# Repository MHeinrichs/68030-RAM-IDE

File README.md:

[This project moved to gitlab on the day M$ bought github](https://gitlab.com/MHeinrichs/68030-RAM-IDE)

The new repository is at: https://gitlab.com/MHeinrichs/68030-RAM-IDE

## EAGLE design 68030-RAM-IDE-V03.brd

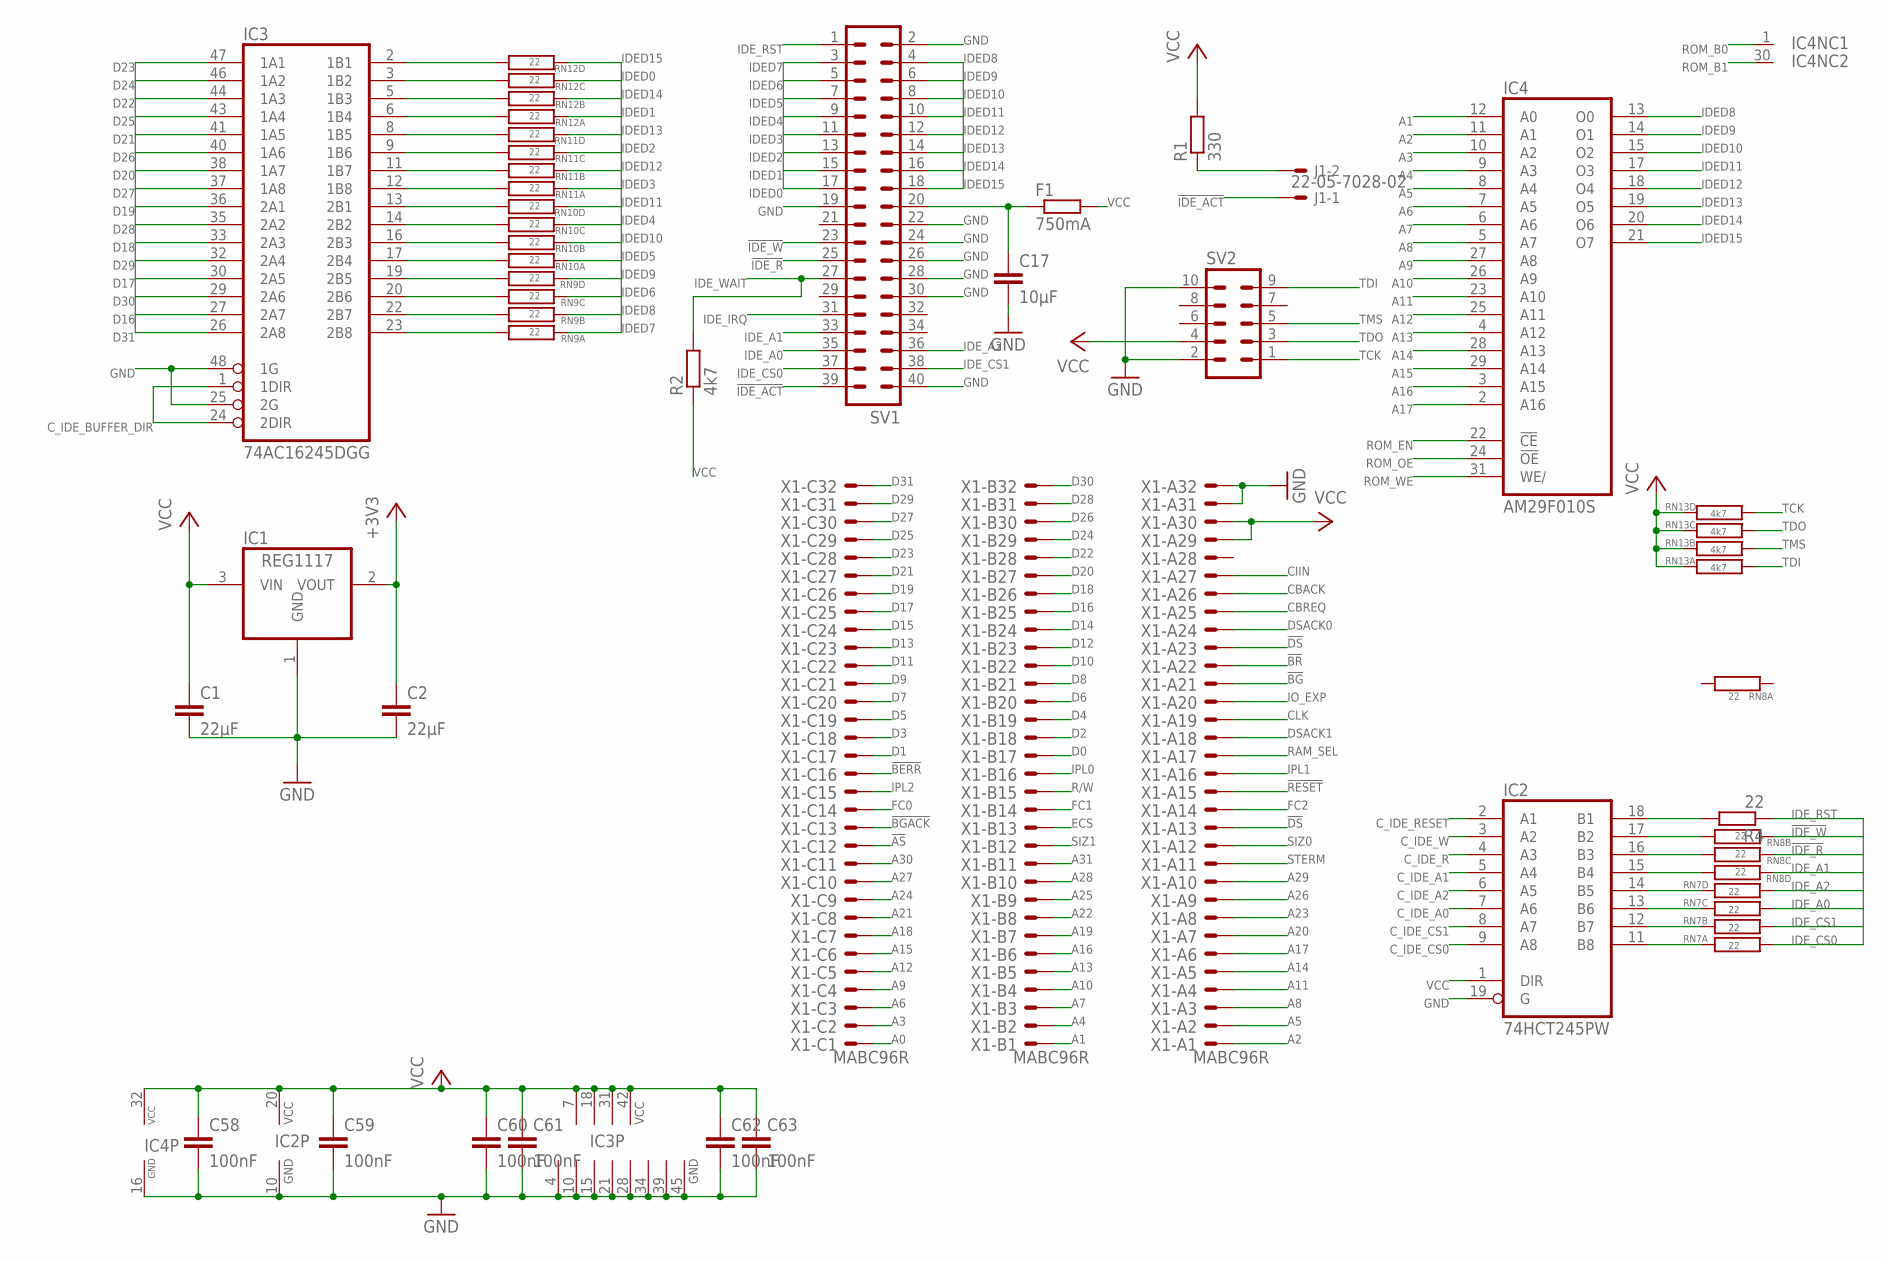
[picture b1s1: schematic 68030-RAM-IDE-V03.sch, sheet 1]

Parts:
C1, C2: 22µF; C1210K
C17: 10µF; C0805K
C58, C59, C60, C61, C62, C63: 100nF; C0805K
F1: 750mA; R2512
IC1: REG1117; SOT223
IC2: 74HCT245PW; TSSOP20
IC3: 74AC16245DGG; TSSOP48
IC4: AM29F010S; PLCC-SR32
J1: 22-05-7028-02; 7395-02
R1: 330; R0805
R2: 4k7; R0805
R4: 22; R0805
RN7, RN8, RN9, RN10, RN11, RN12: 22; R-NETZ@2
RN13: 4k7; R-NETZ@2
SV1: ML40
SV2: ML10
X1: MABC96R

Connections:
!AS: X1.C12; also elsewhere on the board
!BERR: X1.C16
!BG: X1.A21
!BGACK: X1.C13
!BR: X1.A22
!DS: X1.A13, X1.A23; also elsewhere on the board
!IDE_ACT: J1.1, SV1.39
!IDE_R: RN8.P$6, SV1.25
!IDE_W: RN8.P$7, SV1.23
!RESET: X1.A15; also elsewhere on the board
+3V3: C2.1, IC1.2 (VOUT); also elsewhere on the board
A0: X1.C1; also elsewhere on the board
A1: IC4.12 (A0), X1.B1; also elsewhere on the board
A2: IC4.11 (A1), X1.A1; also elsewhere on the board
A3: IC4.10 (A2), X1.C2; also elsewhere on the board
A4: IC4.9 (A3), X1.B2; also elsewhere on the board
A5: IC4.8 (A4), X1.A2; also elsewhere on the board
A6: IC4.7 (A5), X1.C3; also elsewhere on the board
A7: IC4.6 (A6), X1.B3; also elsewhere on the board
A8: IC4.5 (A7), X1.A3; also elsewhere on the board
A9: IC4.27 (A8), X1.C4; also elsewhere on the board
A10: IC4.26 (A9), X1.B4; also elsewhere on the board
A11: IC4.23 (A10), X1.A4; also elsewhere on the board
A12: IC4.25 (A11), X1.C5; also elsewhere on the board
A13: IC4.4 (A12), X1.B5; also elsewhere on the board
A14: IC4.28 (A13), X1.A5; also elsewhere on the board
A15: IC4.29 (A14), X1.C6; also elsewhere on the board
A16: IC4.3 (A15), X1.B6; also elsewhere on the board
A17: IC4.2 (A16), X1.A6; also elsewhere on the board
A18: X1.C7; also elsewhere on the board
A19: X1.B7; also elsewhere on the board
A20: X1.A7; also elsewhere on the board
A21: X1.C8; also elsewhere on the board
A22: X1.B8; also elsewhere on the board
A23: X1.A8; also elsewhere on the board
A24: X1.C9; also elsewhere on the board
A25: X1.B9; also elsewhere on the board
A26: X1.A9; also elsewhere on the board
A27: X1.C10; also elsewhere on the board
A28: X1.B10; also elsewhere on the board
A29: X1.A10; also elsewhere on the board
A30: X1.C11; also elsewhere on the board
A31: X1.B11; also elsewhere on the board
CBACK: X1.A26; also elsewhere on the board
CBREQ: X1.A25; also elsewhere on the board
CIIN: X1.A27; also elsewhere on the board
CLK: X1.A19; also elsewhere on the board
C_IDE_A0: IC2.7 (A6); also elsewhere on the board
C_IDE_A1: IC2.5 (A4); also elsewhere on the board
C_IDE_A2: IC2.6 (A5); also elsewhere on the board
C_IDE_BUFFER_DIR: IC3.1 (1DIR), IC3.24 (2DIR); also elsewhere on the board
C_IDE_CS0: IC2.9 (A8); also elsewhere on the board
C_IDE_CS1: IC2.8 (A7); also elsewhere on the board
C_IDE_R: IC2.4 (A3); also elsewhere on the board
C_IDE_RESET: IC2.2 (A1); also elsewhere on the board
C_IDE_W: IC2.3 (A2); also elsewhere on the board
D0: X1.B17; also elsewhere on the board
D1: X1.C17; also elsewhere on the board
D2: X1.B18; also elsewhere on the board
D3: X1.C18; also elsewhere on the board
D4: X1.B19; also elsewhere on the board
D5: X1.C19; also elsewhere on the board
D6: X1.B20; also elsewhere on the board
D7: X1.C20; also elsewhere on the board
D8: X1.B21; also elsewhere on the board
D9: X1.C21; also elsewhere on the board
D10: X1.B22; also elsewhere on the board
D11: X1.C22; also elsewhere on the board
D12: X1.B23; also elsewhere on the board
D13: X1.C23; also elsewhere on the board
D14: X1.B24; also elsewhere on the board
D15: X1.C24; also elsewhere on the board
D16: IC3.27 (2A7), X1.B25; also elsewhere on the board
D17: IC3.30 (2A5), X1.C25; also elsewhere on the board
D18: IC3.33 (2A3), X1.B26; also elsewhere on the board
D19: IC3.36 (2A1), X1.C26; also elsewhere on the board
D20: IC3.38 (1A7), X1.B27; also elsewhere on the board
D21: IC3.41 (1A5), X1.C27; also elsewhere on the board
D22: IC3.44 (1A3), X1.B28; also elsewhere on the board
D23: IC3.47 (1A1), X1.C28; also elsewhere on the board
D24: IC3.46 (1A2), X1.B29; also elsewhere on the board
D25: IC3.43 (1A4), X1.C29; also elsewhere on the board
D26: IC3.40 (1A6), X1.B30; also elsewhere on the board
D27: IC3.37 (1A8), X1.C30; also elsewhere on the board
D28: IC3.35 (2A2), X1.B31; also elsewhere on the board
D29: IC3.32 (2A4), X1.C31; also elsewhere on the board
D30: IC3.29 (2A6), X1.B32; also elsewhere on the board
D31: IC3.26 (2A8), X1.C32; also elsewhere on the board
DSACK0: X1.A24; also elsewhere on the board
DSACK1: X1.A18; also elsewhere on the board
ECS: X1.B13; also elsewhere on the board
FC0: X1.C14
FC1: X1.B14
FC2: X1.A14
GND: C1.2, C2.2, C17.2, C58.2, C59.2, C60.2, C61.2, C62.2, C63.2, IC1.1 (GND), IC2.10 (GND), IC2.19 (G), IC3.4 (GND), IC3.10 (GND), IC3.15 (GND), IC3.21 (GND), IC3.25 (2G), IC3.28 (GND), IC3.34 (GND), IC3.39 (GND), IC3.45 (GND), IC3.48 (1G), IC4.16 (GND), SV1.2, SV1.19, SV1.22, SV1.24, SV1.26, SV1.28, SV1.30, SV1.40, SV2.2, SV2.10, X1.A31, X1.A32; also elsewhere on the board
IDED0: RN12.P$6, SV1.17
IDED1: RN12.P$8, SV1.15
IDED2: RN11.P$6, SV1.13
IDED3: RN11.P$8, SV1.11
IDED4: RN10.P$6, SV1.9
IDED5: RN10.P$8, SV1.7
IDED6: RN9.P$6, SV1.5
IDED7: RN9.P$8, SV1.3
IDED8: IC4.13 (O0), RN9.P$7, SV1.4
IDED9: IC4.14 (O1), RN9.P$5, SV1.6
IDED10: IC4.15 (O2), RN10.P$7, SV1.8
IDED11: IC4.17 (O3), RN10.P$5, SV1.10
IDED12: IC4.18 (O4), RN11.P$7, SV1.12
IDED13: IC4.19 (O5), RN11.P$5, SV1.14
IDED14: IC4.20 (O6), RN12.P$7, SV1.16
IDED15: IC4.21 (O7), RN12.P$5, SV1.18
IDE_A0: RN7.P$3, SV1.35
IDE_A1: RN8.P$5, SV1.33
IDE_A2: RN7.P$4, SV1.36
IDE_CS0: RN7.P$1, SV1.37
IDE_CS1: RN7.P$2, SV1.38
IDE_IRQ: SV1.31
IDE_RST: R4.1, SV1.1
IDE_WAIT: R2.2, SV1.27; also elsewhere on the board
IO_EXP: X1.A20
IPL0: X1.B16
IPL1: X1.A16
IPL2: X1.C15
KEY_PIN_POWER: C17.1, F1.1, SV1.20
unnamed: IC2.12 (B7), RN7.P$7
unnamed: IC2.11 (B8), RN7.P$8
unnamed: IC2.14 (B5), RN7.P$5
unnamed: IC2.13 (B6), RN7.P$6
unnamed: IC2.16 (B3), RN8.P$3
unnamed: IC2.15 (B4), RN8.P$4
unnamed: IC2.18 (B1), R4.2
unnamed: IC2.17 (B2), RN8.P$2
unnamed: IC3.5 (1B3), RN12.P$2
unnamed: IC3.6 (1B4), RN12.P$1
unnamed: IC3.2 (1B1), RN12.P$4
unnamed: IC3.3 (1B2), RN12.P$3
unnamed: IC3.11 (1B7), RN11.P$2
unnamed: IC3.12 (1B8), RN11.P$1
unnamed: IC3.8 (1B5), RN11.P$4
unnamed: IC3.9 (1B6), RN11.P$3
unnamed: IC3.16 (2B3), RN10.P$2
unnamed: IC3.17 (2B4), RN10.P$1
unnamed: IC3.13 (2B1), RN10.P$4
unnamed: IC3.14 (2B2), RN10.P$3
unnamed: J1.2, R1.1
unnamed: IC3.22 (2B7), RN9.P$2
unnamed: IC3.23 (2B8), RN9.P$1
unnamed: IC3.19 (2B5), RN9.P$4
unnamed: IC3.20 (2B6), RN9.P$3
R/W: X1.B15; also elsewhere on the board
RAM_SEL: X1.A17; also elsewhere on the board
ROM_B0: IC4.1 (NC); also elsewhere on the board
ROM_B1: IC4.30 (NC); also elsewhere on the board
ROM_EN: IC4.22 (!CE); also elsewhere on the board
ROM_OE: IC4.24 (!OE); also elsewhere on the board
ROM_WE: IC4.31 (WE/); also elsewhere on the board
SIZ0: X1.A12; also elsewhere on the board
SIZ1: X1.B12; also elsewhere on the board
STERM: X1.A11; also elsewhere on the board
TCK: RN13.P$4, SV2.1; also elsewhere on the board
TDI: RN13.P$1, SV2.9; also elsewhere on the board
TDO: RN13.P$3, SV2.3; also elsewhere on the board
TMS: RN13.P$2, SV2.5; also elsewhere on the board
VCC: C1.1, C58.1, C59.1, C60.1, C61.1, C62.1, C63.1, F1.2, IC1.3 (VIN), IC2.1 (DIR), IC2.20 (VCC), IC3.7 (VCC), IC3.18 (VCC), IC3.31 (VCC), IC3.42 (VCC), IC4.32 (VCC), R1.2, R2.1, RN13.P$5, RN13.P$6, RN13.P$7, RN13.P$8, SV2.4, X1.A29, X1.A30; also elsewhere on the board

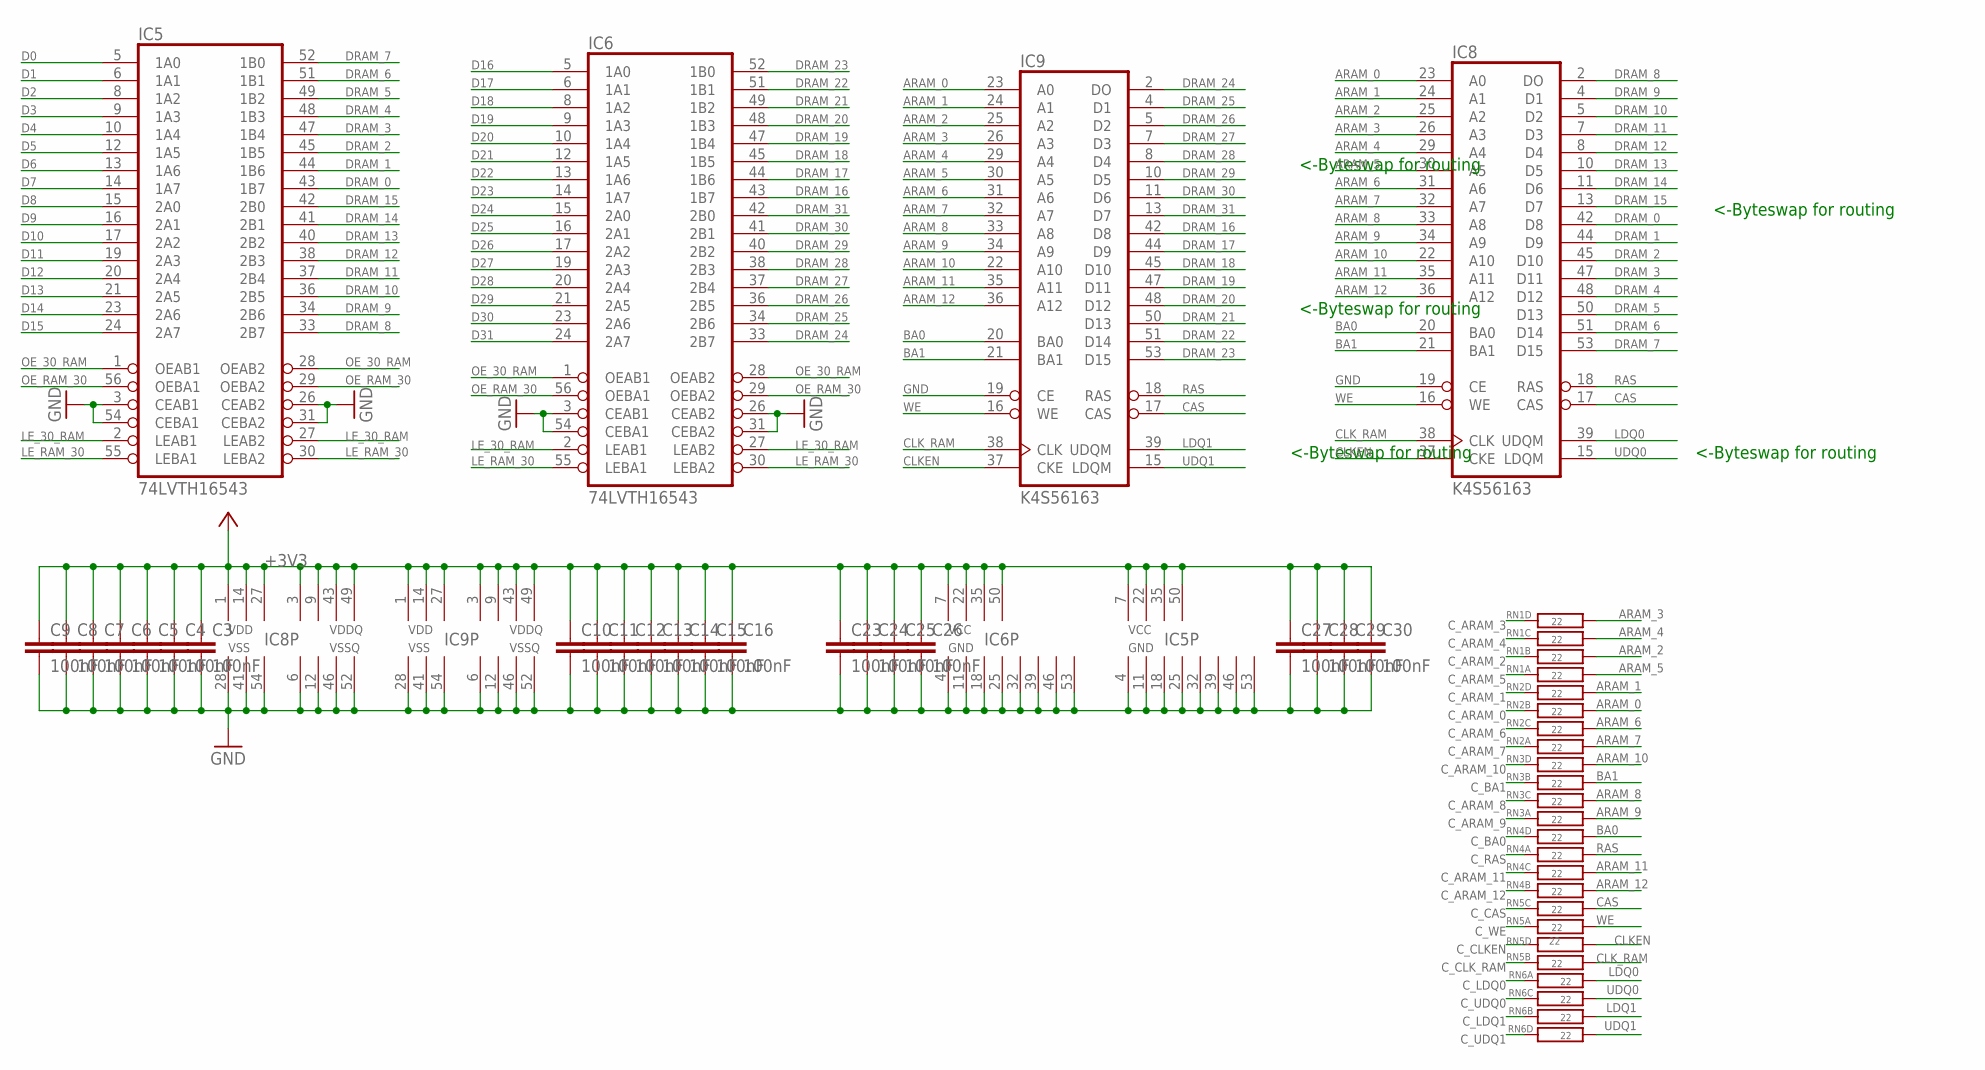
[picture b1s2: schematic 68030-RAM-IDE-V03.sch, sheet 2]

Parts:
C3, C4, C5, C6, C7, C8, C9, C10, C11, C12, C13, C14, C15, C16, C23, C24, C25, C26, C27, C28, C29, C30: 100nF; C0805K
IC5, IC6: 74LVTH16543; TSSOP56@2
IC8, IC9: K4S56163; TSOP2-54@2
RN1, RN2, RN3, RN4, RN5, RN6: 22; R-NETZ@2

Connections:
+3V3: C3.1, C4.1, C5.1, C6.1, C7.1, C8.1, C9.1, C10.1, C11.1, C12.1, C13.1, C14.1, C15.1, C16.1, C23.1, C24.1, C25.1, C26.1, C27.1, C28.1, C29.1, C30.1, IC5.7 (VCC), IC5.22 (VCC), IC5.35 (VCC), IC5.50 (VCC), IC6.7 (VCC), IC6.22 (VCC), IC6.35 (VCC), IC6.50 (VCC), IC8.1 (VCC), IC8.3 (VCC), IC8.9 (VCC), IC8.14 (VCC), IC8.27 (VCC), IC8.43 (VCC), IC8.49 (VCC), IC9.1 (VCC), IC9.3 (VCC), IC9.9 (VCC), IC9.14 (VCC), IC9.27 (VCC), IC9.43 (VCC), IC9.49 (VCC); also elsewhere on the board
ARAM_0: IC8.23 (A0), IC9.23 (A0), RN2.P$2
ARAM_1: IC8.24 (A1), IC9.24 (A1), RN2.P$4
ARAM_2: IC8.25 (A2), IC9.25 (A2), RN1.P$2
ARAM_3: IC8.26 (A3), IC9.26 (A3), RN1.P$4
ARAM_4: IC8.29 (A4), IC9.29 (A4), RN1.P$3
ARAM_5: IC8.30 (A5), IC9.30 (A5), RN1.P$1
ARAM_6: IC8.31 (A6), IC9.31 (A6), RN2.P$3
ARAM_7: IC8.32 (A7), IC9.32 (A7), RN2.P$1
ARAM_8: IC8.33 (A8), IC9.33 (A8), RN3.P$3
ARAM_9: IC8.34 (A9), IC9.34 (A9), RN3.P$1
ARAM_10: IC8.22 (A10), IC9.22 (A10), RN3.P$4
ARAM_11: IC8.35 (A11), IC9.35 (A11), RN4.P$3
ARAM_12: IC8.36 (A12), IC9.36 (A12), RN4.P$2
BA0: IC8.20 (BA0), IC9.20 (BA0), RN4.P$4
BA1: IC8.21 (BA1), IC9.21 (BA1), RN3.P$2
CAS: IC8.17 (CAS), IC9.17 (CAS), RN5.P$3
CLKEN: IC8.37 (CKE), IC9.37 (CKE), RN5.P$4
CLK_RAM: IC8.38 (CLK), IC9.38 (CLK), RN5.P$2
C_ARAM_0: RN2.P$7; also elsewhere on the board
C_ARAM_1: RN2.P$5; also elsewhere on the board
C_ARAM_2: RN1.P$7; also elsewhere on the board
C_ARAM_3: RN1.P$5; also elsewhere on the board
C_ARAM_4: RN1.P$6; also elsewhere on the board
C_ARAM_5: RN1.P$8; also elsewhere on the board
C_ARAM_6: RN2.P$6; also elsewhere on the board
C_ARAM_7: RN2.P$8; also elsewhere on the board
C_ARAM_8: RN3.P$6; also elsewhere on the board
C_ARAM_9: RN3.P$8; also elsewhere on the board
C_ARAM_10: RN3.P$5; also elsewhere on the board
C_ARAM_11: RN4.P$6; also elsewhere on the board
C_ARAM_12: RN4.P$7; also elsewhere on the board
C_BA0: RN4.P$5; also elsewhere on the board
C_BA1: RN3.P$7; also elsewhere on the board
C_CAS: RN5.P$6; also elsewhere on the board
C_CLKEN: RN5.P$5; also elsewhere on the board
C_CLK_RAM: RN5.P$7; also elsewhere on the board
C_LDQ0: RN6.P$1; also elsewhere on the board
C_LDQ1: RN6.P$2; also elsewhere on the board
C_RAS: RN4.P$8; also elsewhere on the board
C_UDQ0: RN6.P$3; also elsewhere on the board
C_UDQ1: RN6.P$4; also elsewhere on the board
C_WE: RN5.P$8; also elsewhere on the board
D0: IC5.5 (1A0); also elsewhere on the board
D1: IC5.6 (1A1); also elsewhere on the board
D2: IC5.8 (1A2); also elsewhere on the board
D3: IC5.9 (1A3); also elsewhere on the board
D4: IC5.10 (1A4); also elsewhere on the board
D5: IC5.12 (1A5); also elsewhere on the board
D6: IC5.13 (1A6); also elsewhere on the board
D7: IC5.14 (1A7); also elsewhere on the board
D8: IC5.15 (2A0); also elsewhere on the board
D9: IC5.16 (2A1); also elsewhere on the board
D10: IC5.17 (2A2); also elsewhere on the board
D11: IC5.19 (2A3); also elsewhere on the board
D12: IC5.20 (2A4); also elsewhere on the board
D13: IC5.21 (2A5); also elsewhere on the board
D14: IC5.23 (2A6); also elsewhere on the board
D15: IC5.24 (2A7); also elsewhere on the board
D16: IC6.5 (1A0); also elsewhere on the board
D17: IC6.6 (1A1); also elsewhere on the board
D18: IC6.8 (1A2); also elsewhere on the board
D19: IC6.9 (1A3); also elsewhere on the board
D20: IC6.10 (1A4); also elsewhere on the board
D21: IC6.12 (1A5); also elsewhere on the board
D22: IC6.13 (1A6); also elsewhere on the board
D23: IC6.14 (1A7); also elsewhere on the board
D24: IC6.15 (2A0); also elsewhere on the board
D25: IC6.16 (2A1); also elsewhere on the board
D26: IC6.17 (2A2); also elsewhere on the board
D27: IC6.19 (2A3); also elsewhere on the board
D28: IC6.20 (2A4); also elsewhere on the board
D29: IC6.21 (2A5); also elsewhere on the board
D30: IC6.23 (2A6); also elsewhere on the board
D31: IC6.24 (2A7); also elsewhere on the board
DRAM_0: IC5.43 (1B7), IC8.42 (D8)
DRAM_1: IC5.44 (1B6), IC8.44 (D9)
DRAM_2: IC5.45 (1B5), IC8.45 (D10)
DRAM_3: IC5.47 (1B4), IC8.47 (D11)
DRAM_4: IC5.48 (1B3), IC8.48 (D12)
DRAM_5: IC5.49 (1B2), IC8.50 (D13)
DRAM_6: IC5.51 (1B1), IC8.51 (D14)
DRAM_7: IC5.52 (1B0), IC8.53 (D15)
DRAM_8: IC5.33 (2B7), IC8.2 (DO)
DRAM_9: IC5.34 (2B6), IC8.4 (D1)
DRAM_10: IC5.36 (2B5), IC8.5 (D2)
DRAM_11: IC5.37 (2B4), IC8.7 (D3)
DRAM_12: IC5.38 (2B3), IC8.8 (D4)
DRAM_13: IC5.40 (2B2), IC8.10 (D5)
DRAM_14: IC5.41 (2B1), IC8.11 (D6)
DRAM_15: IC5.42 (2B0), IC8.13 (D7)
DRAM_16: IC6.43 (1B7), IC9.42 (D8)
DRAM_17: IC6.44 (1B6), IC9.44 (D9)
DRAM_18: IC6.45 (1B5), IC9.45 (D10)
DRAM_19: IC6.47 (1B4), IC9.47 (D11)
DRAM_20: IC6.48 (1B3), IC9.48 (D12)
DRAM_21: IC6.49 (1B2), IC9.50 (D13)
DRAM_22: IC6.51 (1B1), IC9.51 (D14)
DRAM_23: IC6.52 (1B0), IC9.53 (D15)
DRAM_24: IC6.33 (2B7), IC9.2 (DO)
DRAM_25: IC6.34 (2B6), IC9.4 (D1)
DRAM_26: IC6.36 (2B5), IC9.5 (D2)
DRAM_27: IC6.37 (2B4), IC9.7 (D3)
DRAM_28: IC6.38 (2B3), IC9.8 (D4)
DRAM_29: IC6.40 (2B2), IC9.10 (D5)
DRAM_30: IC6.41 (2B1), IC9.11 (D6)
DRAM_31: IC6.42 (2B0), IC9.13 (D7)
GND: C3.2, C4.2, C5.2, C6.2, C7.2, C8.2, C9.2, C10.2, C11.2, C12.2, C13.2, C14.2, C15.2, C16.2, C23.2, C24.2, C25.2, C26.2, C27.2, C28.2, C29.2, C30.2, IC5.3 (CEAB1), IC5.4 (GND), IC5.11 (GND), IC5.18 (GND), IC5.25 (GND), IC5.26 (CEAB2), IC5.31 (CEBA2), IC5.32 (GND), IC5.39 (GND), IC5.46 (GND), IC5.53 (GND), IC5.54 (CEBA1), IC6.3 (CEAB1), IC6.4 (GND), IC6.11 (GND), IC6.18 (GND), IC6.25 (GND), IC6.26 (CEAB2), IC6.31 (CEBA2), IC6.32 (GND), IC6.39 (GND), IC6.46 (GND), IC6.53 (GND), IC6.54 (CEBA1), IC8.6 (GND), IC8.12 (GND), IC8.19 (CE), IC8.28 (GND), IC8.41 (GND), IC8.46 (GND), IC8.52 (GND), IC8.54 (GND), IC9.6 (GND), IC9.12 (GND), IC9.19 (CE), IC9.28 (GND), IC9.41 (GND), IC9.46 (GND), IC9.52 (GND), IC9.54 (GND); also elsewhere on the board
LDQ0: IC8.39 (UDQM), RN6.P$8
LDQ1: IC9.39 (UDQM), RN6.P$7
LE_30_RAM: IC5.2 (LEAB1), IC5.27 (LEAB2), IC6.2 (LEAB1), IC6.27 (LEAB2); also elsewhere on the board
LE_RAM_30: IC5.30 (LEBA2), IC5.55 (LEBA1), IC6.30 (LEBA2), IC6.55 (LEBA1); also elsewhere on the board
OE_30_RAM: IC5.1 (OEAB1), IC5.28 (OEAB2), IC6.1 (OEAB1), IC6.28 (OEAB2); also elsewhere on the board
OE_RAM_30: IC5.29 (OEBA2), IC5.56 (OEBA1), IC6.29 (OEBA2), IC6.56 (OEBA1); also elsewhere on the board
RAS: IC8.18 (RAS), IC9.18 (RAS), RN4.P$1
UDQ0: IC8.15 (LDQM), RN6.P$6
UDQ1: IC9.15 (LDQM), RN6.P$5
WE: IC8.16 (WE), IC9.16 (WE), RN5.P$1

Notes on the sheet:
<-Byteswap for routing

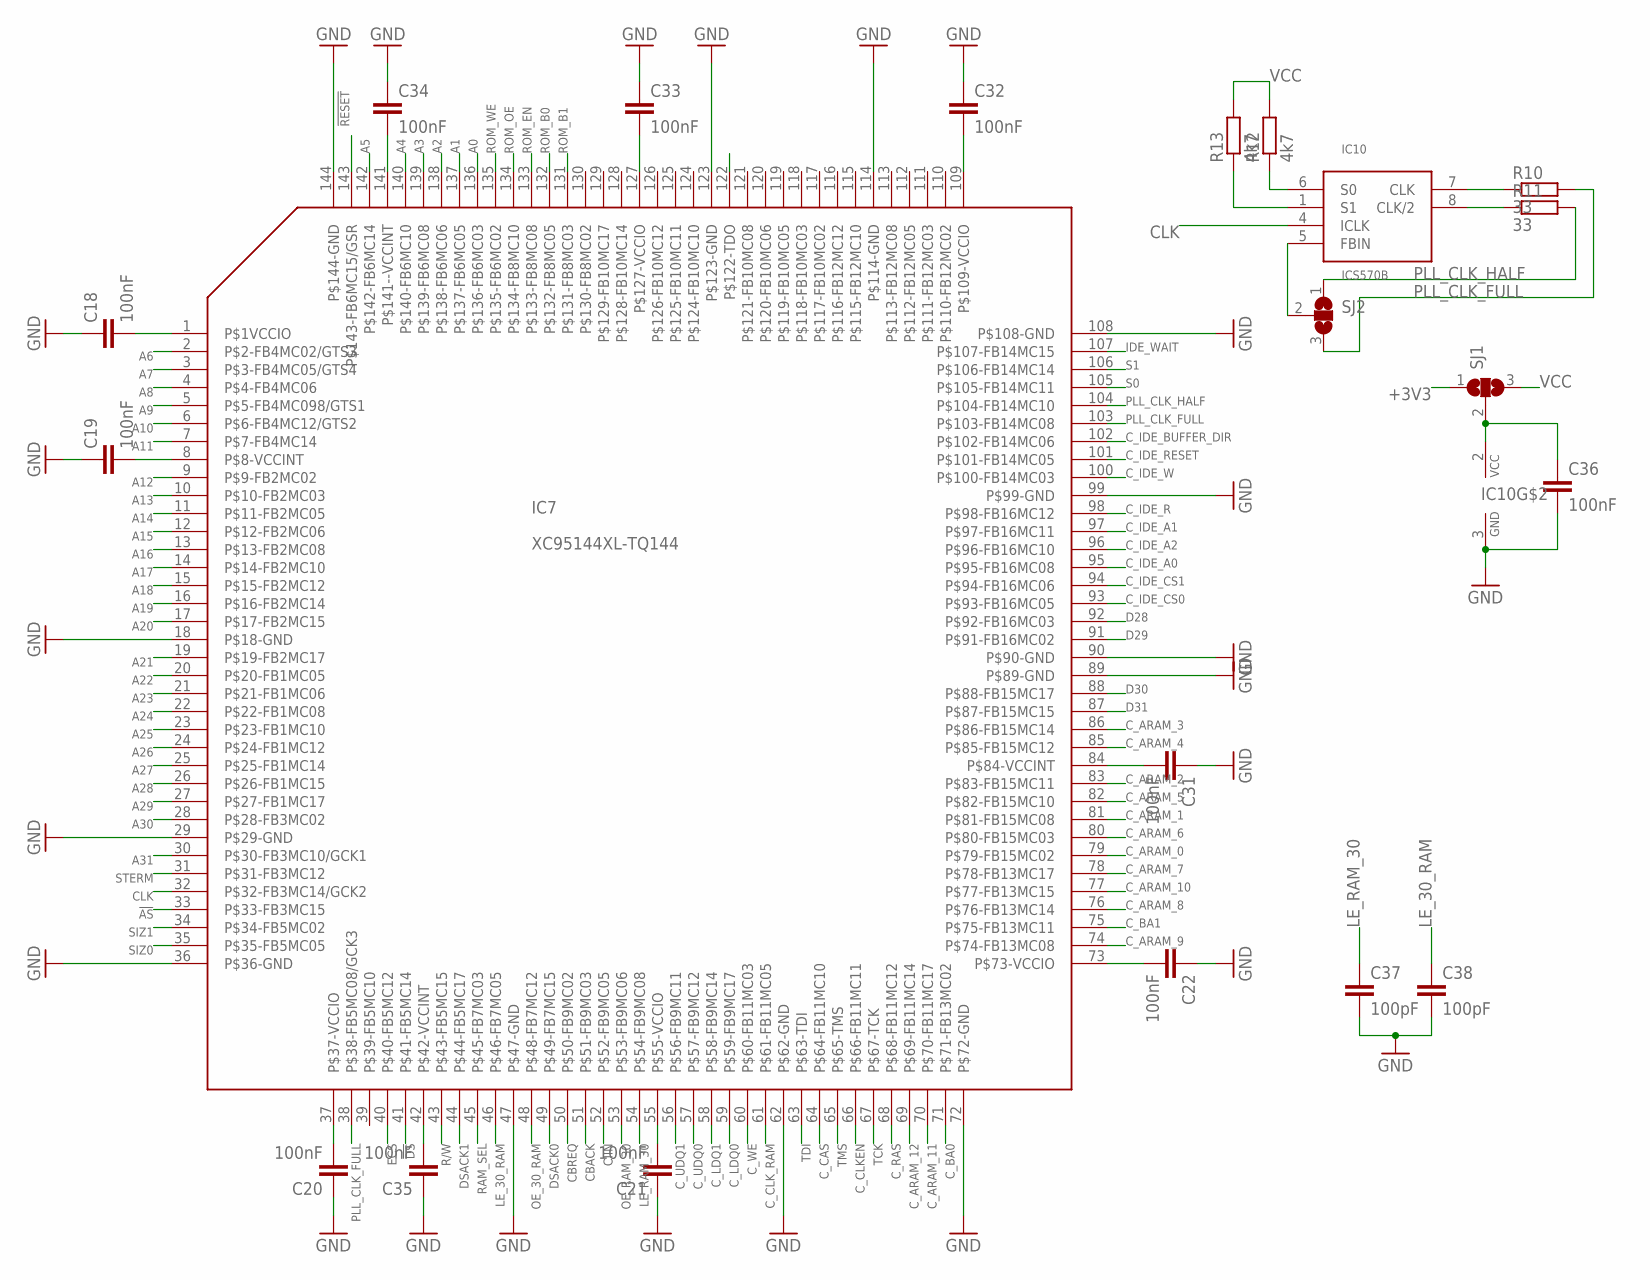
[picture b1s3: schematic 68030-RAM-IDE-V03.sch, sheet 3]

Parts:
C18, C19, C20, C21, C22, C31, C32, C33, C34, C35, C36: 100nF; C0805K
C37, C38: 100pF; C0805K
IC7: XC95144XL-TQ144; TQFP144
IC10: ICS570B; SO-8
R10, R11: 33; R0805
R12, R13: 4k7; R0805
SJ1, SJ2: SJ2W; SJ_2

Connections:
!AS: IC7.33 (P$33-FB3MC15); also elsewhere on the board
!DS: IC7.41 (P$41-FB5MC14); also elsewhere on the board
!RESET: IC7.143 (P$143-FB6MC15/GSR); also elsewhere on the board
+3V3: C18.2, C19.2, C20.2, C21.2, C22.2, C31.2, C32.2, C33.2, C34.2, C35.2, IC7.1 (P$1VCCIO), IC7.8 (P$8-VCCINT), IC7.37 (P$37-VCCIO), IC7.42 (P$42-VCCINT), IC7.55 (P$55-VCCIO), IC7.73 (P$73-VCCIO), IC7.84 (P$84-VCCINT), IC7.109 (P$109-VCCIO), IC7.127 (P$127-VCCIO), IC7.141 (P$141--VCCINT), SJ1.1; also elsewhere on the board
A0: IC7.136 (P$136-FB6MC03); also elsewhere on the board
A1: IC7.137 (P$137-FB6MC05); also elsewhere on the board
A2: IC7.138 (P$138-FB6MC06); also elsewhere on the board
A3: IC7.139 (P$139-FB6MC08); also elsewhere on the board
A4: IC7.140 (P$140-FB6MC10); also elsewhere on the board
A5: IC7.142 (P$142-FB6MC14); also elsewhere on the board
A6: IC7.2 (P$2-FB4MC02/GTS3); also elsewhere on the board
A7: IC7.3 (P$3-FB4MC05/GTS4); also elsewhere on the board
A8: IC7.4 (P$4-FB4MC06); also elsewhere on the board
A9: IC7.5 (P$5-FB4MC098/GTS1); also elsewhere on the board
A10: IC7.6 (P$6-FB4MC12/GTS2); also elsewhere on the board
A11: IC7.7 (P$7-FB4MC14); also elsewhere on the board
A12: IC7.9 (P$9-FB2MC02); also elsewhere on the board
A13: IC7.10 (P$10-FB2MC03); also elsewhere on the board
A14: IC7.11 (P$11-FB2MC05); also elsewhere on the board
A15: IC7.12 (P$12-FB2MC06); also elsewhere on the board
A16: IC7.13 (P$13-FB2MC08); also elsewhere on the board
A17: IC7.14 (P$14-FB2MC10); also elsewhere on the board
A18: IC7.15 (P$15-FB2MC12); also elsewhere on the board
A19: IC7.16 (P$16-FB2MC14); also elsewhere on the board
A20: IC7.17 (P$17-FB2MC15); also elsewhere on the board
A21: IC7.19 (P$19-FB2MC17); also elsewhere on the board
A22: IC7.20 (P$20-FB1MC05); also elsewhere on the board
A23: IC7.21 (P$21-FB1MC06); also elsewhere on the board
A24: IC7.22 (P$22-FB1MC08); also elsewhere on the board
A25: IC7.23 (P$23-FB1MC10); also elsewhere on the board
A26: IC7.24 (P$24-FB1MC12); also elsewhere on the board
A27: IC7.25 (P$25-FB1MC14); also elsewhere on the board
A28: IC7.26 (P$26-FB1MC15); also elsewhere on the board
A29: IC7.27 (P$27-FB1MC17); also elsewhere on the board
A30: IC7.28 (P$28-FB3MC02); also elsewhere on the board
A31: IC7.30 (P$30-FB3MC10/GCK1); also elsewhere on the board
CBACK: IC7.51 (P$51-FB9MC03); also elsewhere on the board
CBREQ: IC7.50 (P$50-FB9MC02); also elsewhere on the board
CIIN: IC7.52 (P$52-FB9MC05); also elsewhere on the board
CLK: IC7.32 (P$32-FB3MC14/GCK2), IC10.4 (ICLK); also elsewhere on the board
C_ARAM_0: IC7.79 (P$79-FB15MC02); also elsewhere on the board
C_ARAM_1: IC7.81 (P$81-FB15MC08); also elsewhere on the board
C_ARAM_2: IC7.83 (P$83-FB15MC11); also elsewhere on the board
C_ARAM_3: IC7.86 (P$86-FB15MC14); also elsewhere on the board
C_ARAM_4: IC7.85 (P$85-FB15MC12); also elsewhere on the board
C_ARAM_5: IC7.82 (P$82-FB15MC10); also elsewhere on the board
C_ARAM_6: IC7.80 (P$80-FB15MC03); also elsewhere on the board
C_ARAM_7: IC7.78 (P$78-FB13MC17); also elsewhere on the board
C_ARAM_8: IC7.76 (P$76-FB13MC14); also elsewhere on the board
C_ARAM_9: IC7.74 (P$74-FB13MC08); also elsewhere on the board
C_ARAM_10: IC7.77 (P$77-FB13MC15); also elsewhere on the board
C_ARAM_11: IC7.70 (P$70-FB11MC17); also elsewhere on the board
C_ARAM_12: IC7.69 (P$69-FB11MC14); also elsewhere on the board
C_BA0: IC7.71 (P$71-FB13MC02); also elsewhere on the board
C_BA1: IC7.75 (P$75-FB13MC11); also elsewhere on the board
C_CAS: IC7.64 (P$64-FB11MC10); also elsewhere on the board
C_CLKEN: IC7.66 (P$66-FB11MC11); also elsewhere on the board
C_CLK_RAM: IC7.61 (P$61-FB11MC05); also elsewhere on the board
C_IDE_A0: IC7.95 (P$95-FB16MC08); also elsewhere on the board
C_IDE_A1: IC7.97 (P$97-FB16MC11); also elsewhere on the board
C_IDE_A2: IC7.96 (P$96-FB16MC10); also elsewhere on the board
C_IDE_BUFFER_DIR: IC7.102 (P$102-FB14MC06); also elsewhere on the board
C_IDE_CS0: IC7.93 (P$93-FB16MC05); also elsewhere on the board
C_IDE_CS1: IC7.94 (P$94-FB16MC06); also elsewhere on the board
C_IDE_R: IC7.98 (P$98-FB16MC12); also elsewhere on the board
C_IDE_RESET: IC7.101 (P$101-FB14MC05); also elsewhere on the board
C_IDE_W: IC7.100 (P$100-FB14MC03); also elsewhere on the board
C_LDQ0: IC7.59 (P$59-FB9MC17); also elsewhere on the board
C_LDQ1: IC7.58 (P$58-FB9MC14); also elsewhere on the board
C_RAS: IC7.68 (P$68-FB11MC12); also elsewhere on the board
C_UDQ0: IC7.57 (P$57-FB9MC12); also elsewhere on the board
C_UDQ1: IC7.56 (P$56-FB9MC11); also elsewhere on the board
C_WE: IC7.60 (P$60-FB11MC03); also elsewhere on the board
D28: IC7.92 (P$92-FB16MC03); also elsewhere on the board
D29: IC7.91 (P$91-FB16MC02); also elsewhere on the board
D30: IC7.88 (P$88-FB15MC17); also elsewhere on the board
D31: IC7.87 (P$87-FB15MC15); also elsewhere on the board
DSACK0: IC7.49 (P$49-FB7MC15); also elsewhere on the board
DSACK1: IC7.44 (P$44-FB5MC17); also elsewhere on the board
ECS: IC7.40 (P$40-FB5MC12); also elsewhere on the board
GND: C18.1, C19.1, C20.1, C21.1, C22.1, C31.1, C32.1, C33.1, C34.1, C35.1, C36.2, C37.2, C38.2, IC7.18 (P$18-GND), IC7.29 (P$29-GND), IC7.36 (P$36-GND), IC7.47 (P$47-GND), IC7.62 (P$62-GND), IC7.72 (P$72-GND), IC7.89 (P$89-GND), IC7.90 (P$90-GND), IC7.99 (P$99-GND), IC7.108 (P$108-GND), IC7.114 (P$114-GND), IC7.123 (P$123-GND), IC7.144 (P$144-GND), IC10.3 (GND); also elsewhere on the board
IDE_WAIT: IC7.107 (P$107-FB14MC15); also elsewhere on the board
LE_30_RAM: C38.1, IC7.46 (P$46-FB7MC05); also elsewhere on the board
LE_RAM_30: C37.1, IC7.54 (P$54-FB9MC08); also elsewhere on the board
unnamed: C36.1, IC10.2 (VCC), SJ1.2
unnamed: IC10.7 (CLK), R10.1
unnamed: IC10.8 (CLK/2), R11.1
unnamed: IC10.5 (FBIN), SJ2.2
OE_30_RAM: IC7.48 (P$48-FB7MC12); also elsewhere on the board
OE_RAM_30: IC7.53 (P$53-FB9MC06); also elsewhere on the board
PLL_CLK_FULL: IC7.38 (P$38-FB5MC08/GCK3), IC7.103 (P$103-FB14MC08), R10.2, SJ2.3
PLL_CLK_HALF: IC7.104 (P$104-FB14MC10), R11.2, SJ2.1
R/W: IC7.43 (P$43-FB5MC15); also elsewhere on the board
RAM_SEL: IC7.45 (P$45-FB7MC03); also elsewhere on the board
ROM_B0: IC7.132 (P$132-FB8MC05); also elsewhere on the board
ROM_B1: IC7.131 (P$131-FB8MC03); also elsewhere on the board
ROM_EN: IC7.133 (P$133-FB8MC08); also elsewhere on the board
ROM_OE: IC7.134 (P$134-FB8MC10); also elsewhere on the board
ROM_WE: IC7.135 (P$135-FB6MC02); also elsewhere on the board
S0: IC7.105 (P$105-FB14MC11), IC10.6 (S0), R12.1
S1: IC7.106 (P$106-FB14MC14), IC10.1 (S1), R13.1
SIZ0: IC7.35 (P$35-FB5MC05); also elsewhere on the board
SIZ1: IC7.34 (P$34-FB5MC02); also elsewhere on the board
STERM: IC7.31 (P$31-FB3MC12); also elsewhere on the board
TCK: IC7.67 (P$67-TCK); also elsewhere on the board
TDI: IC7.63 (P$63-TDI); also elsewhere on the board
TDO: IC7.122 (P$122-TDO); also elsewhere on the board
TMS: IC7.65 (P$65-TMS); also elsewhere on the board
VCC: R12.2, R13.2, SJ1.3; also elsewhere on the board

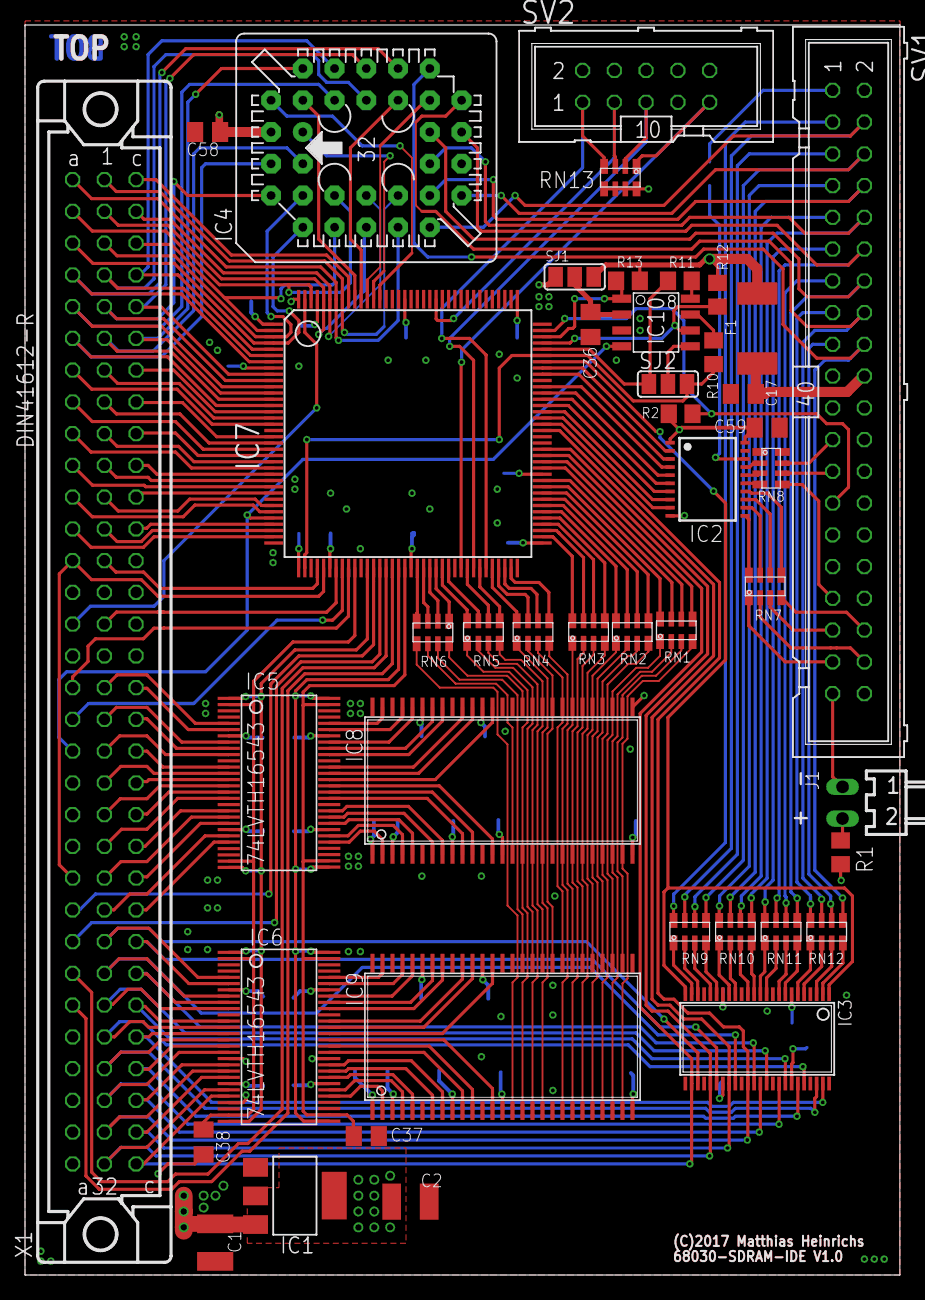
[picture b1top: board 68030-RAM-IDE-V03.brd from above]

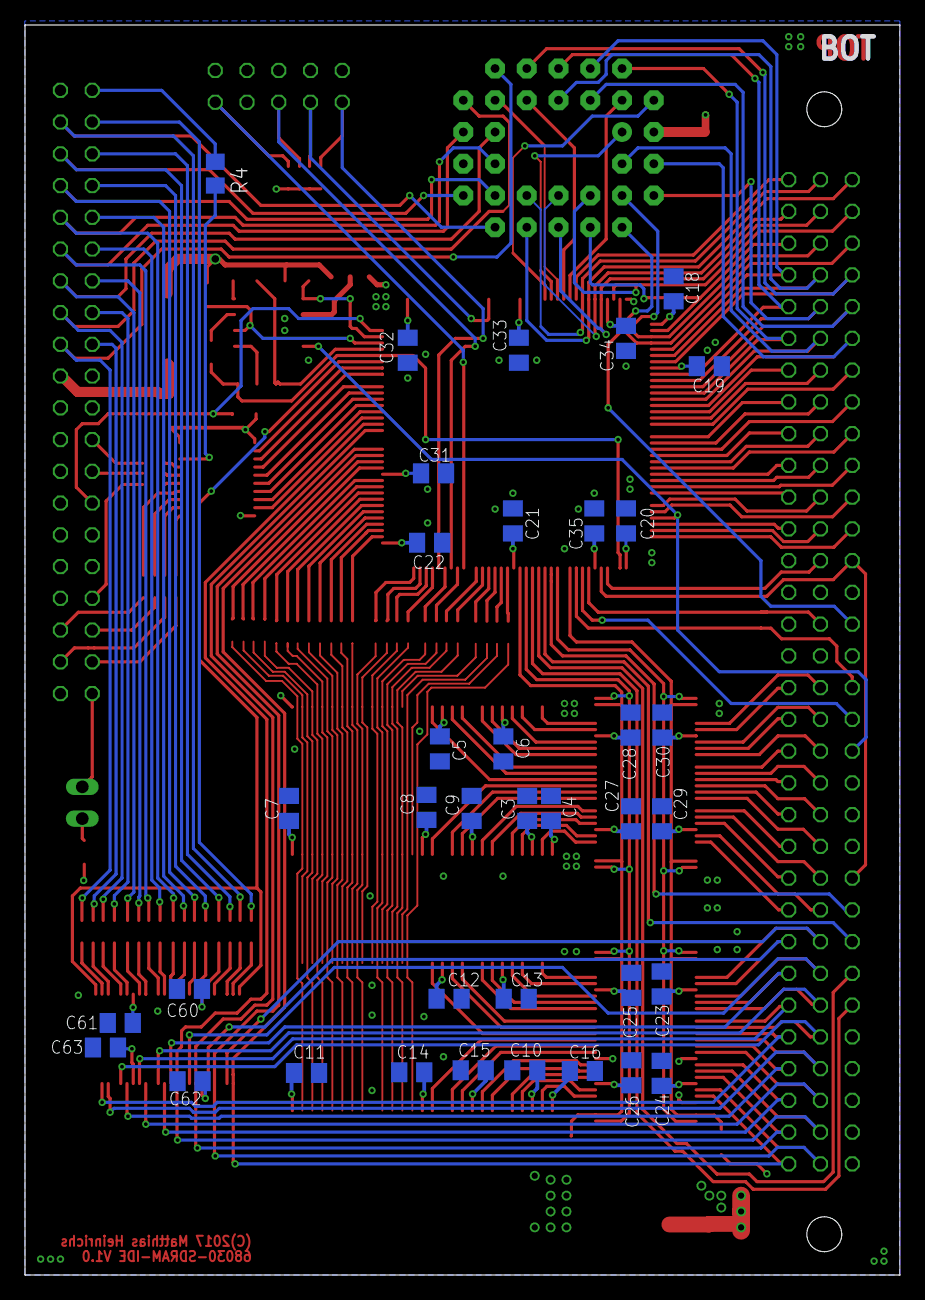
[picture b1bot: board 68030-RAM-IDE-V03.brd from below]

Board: 4 copper layers, 70.0 x 100.0 mm, 81 parts (37 on the bottom side), 244 nets.

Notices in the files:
68030-RAM-IDE-V03.brd:
(C)2017 Matthias Heinrichs
